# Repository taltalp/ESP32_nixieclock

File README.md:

# ESP32 Nixie Clock

## Overview
Nixie-tube Clock using ESP32 KiCad PCB design and Arduino projects.

## Software Versions
- KiCad 4.0.1 Stable
- Arduino 1.8.2

## Nixie Tube footprints
IN-12 is used in this design and this footprint has 2mm hole * 12 which is designed to use IN-12 pin sockets.

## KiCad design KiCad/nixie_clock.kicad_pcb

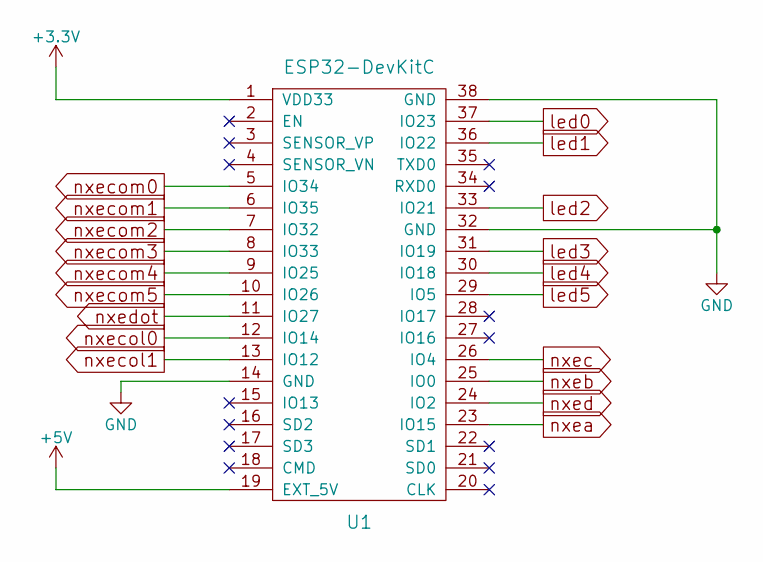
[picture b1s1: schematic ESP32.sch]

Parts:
U1: ESP32-DevKitC; ESP32-DEV-Kit

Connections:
+3V3: U1.1 (VDD33); also elsewhere on the board
+5V: U1.19 (EXT_5V); also elsewhere on the board
GND: U1.14 (GND), U1.32 (GND), U1.38 (GND); also elsewhere on the board
led0: U1.37 (IO23); also elsewhere on the board
led1: U1.36 (IO22); also elsewhere on the board
led2: U1.33 (IO21); also elsewhere on the board
led3: U1.31 (IO19); also elsewhere on the board
led4: U1.30 (IO18); also elsewhere on the board
led5: U1.29 (IO5); also elsewhere on the board
nxea: U1.23 (IO15); also elsewhere on the board
nxeb: U1.25 (IO0); also elsewhere on the board
nxec: U1.26 (IO4); also elsewhere on the board
nxecol0: U1.12 (IO14); also elsewhere on the board
nxecol1: U1.13 (IO12); also elsewhere on the board
nxecom0: U1.5 (IO34); also elsewhere on the board
nxecom1: U1.6 (IO35); also elsewhere on the board
nxecom2: U1.7 (IO32); also elsewhere on the board
nxecom3: U1.8 (IO33); also elsewhere on the board
nxecom4: U1.9 (IO25); also elsewhere on the board
nxecom5: U1.10 (IO26); also elsewhere on the board
nxed: U1.24 (IO2); also elsewhere on the board
nxedot: U1.11 (IO27); also elsewhere on the board

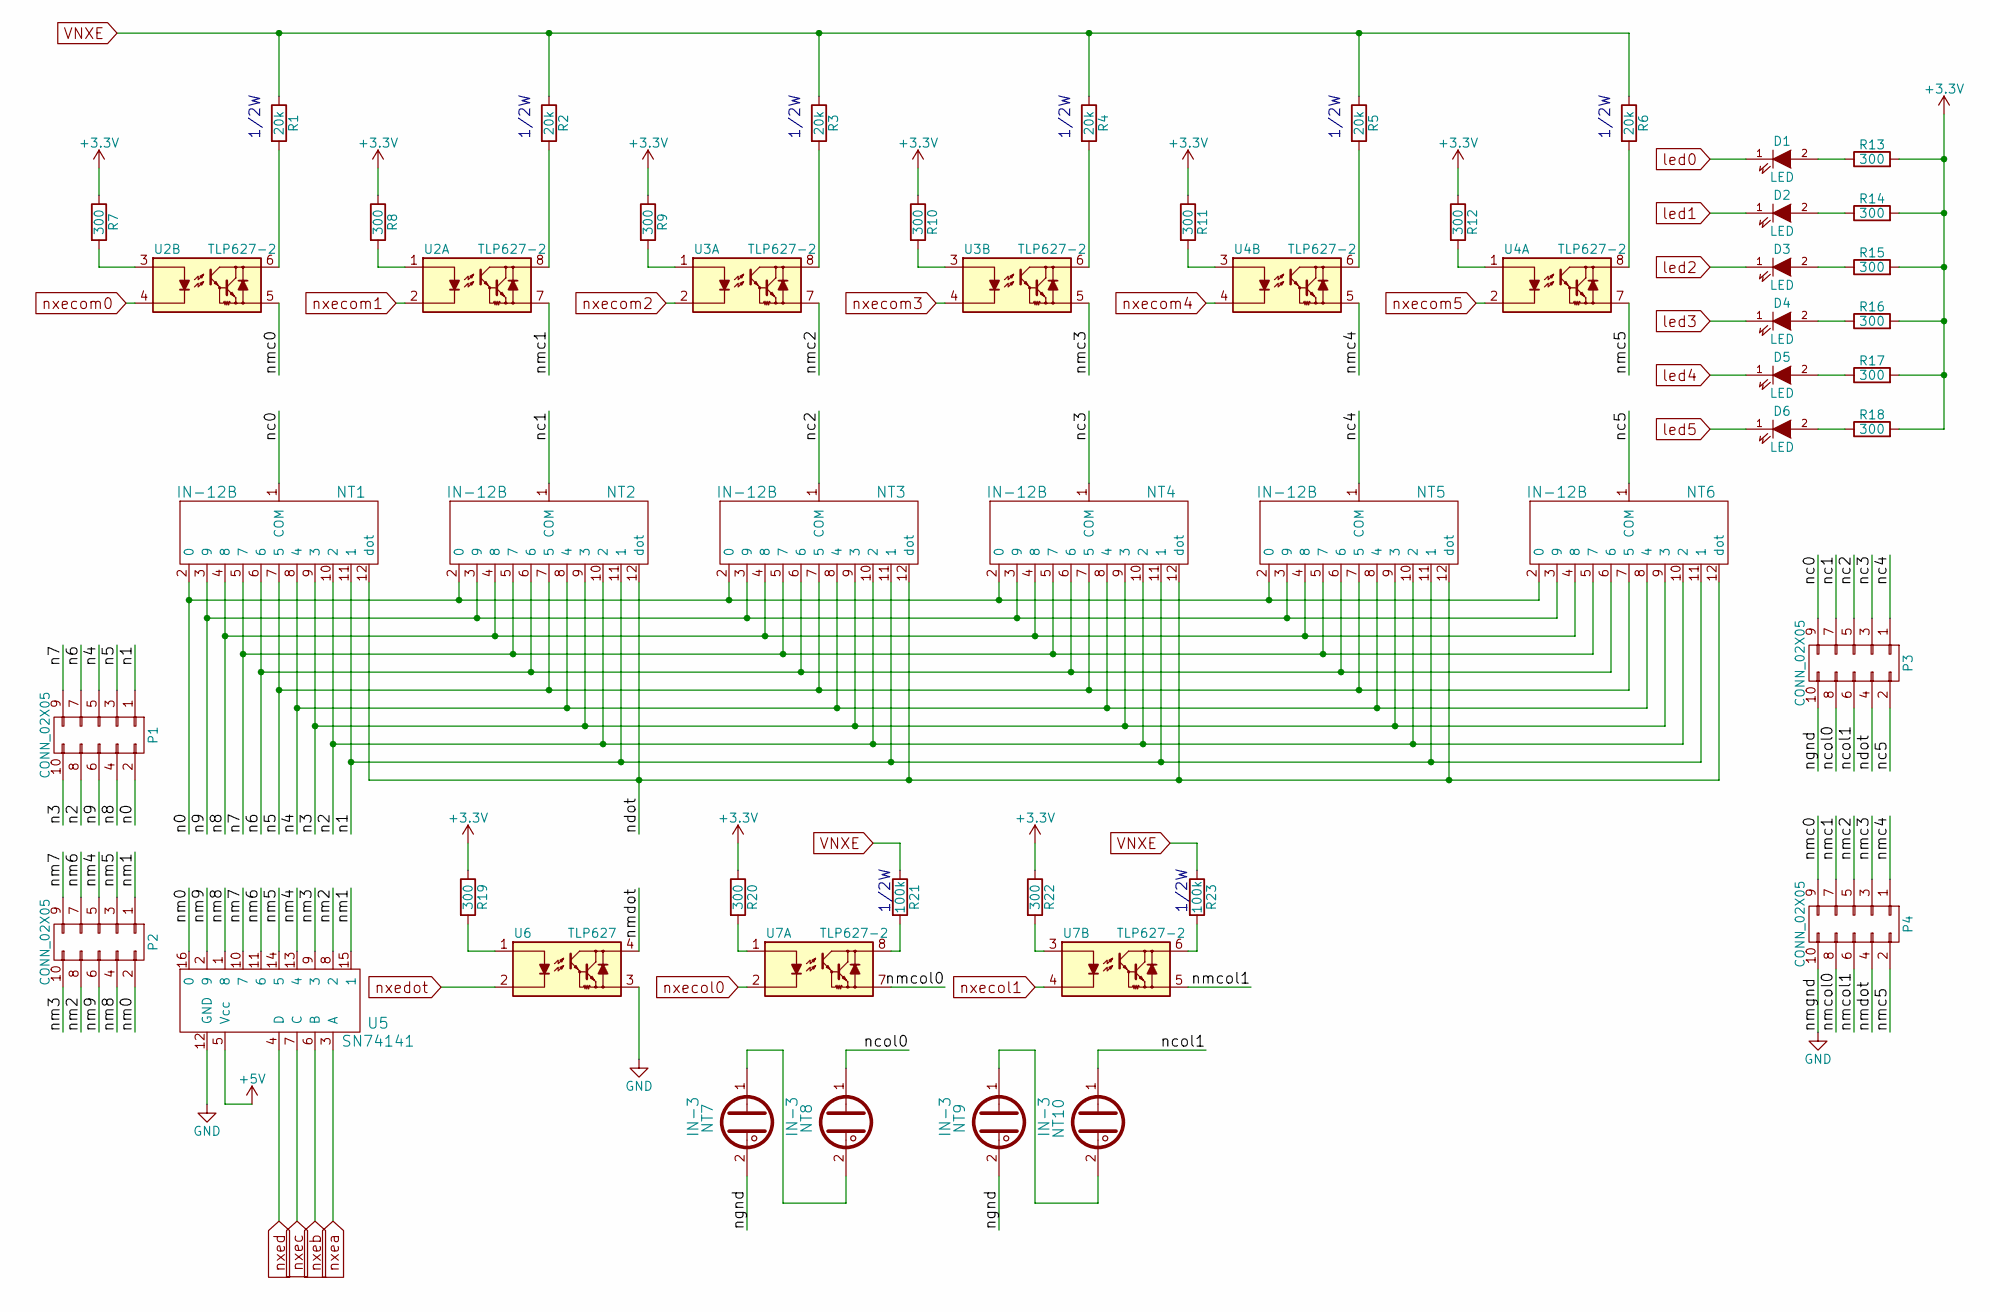
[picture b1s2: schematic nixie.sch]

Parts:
D1, D2, D3, D4, D5, D6: LED; LED_0603
NT1, NT2, NT3, NT4, NT5, NT6: IN-12B; IN-12
NT7, NT8, NT9, NT10: IN-3
P1, P2, P3, P4: CONN_02X05; Socket_Strip_Straight_2x05_Pitch2.54mm
R1, R2, R3, R4, R5, R6: 20k; R_2512
R7, R8, R9, R10, R11, R12, R13, R14, R15, R16, R17, R18, R19, R20, R22: 300; R_0603
R21, R23: 100k; R_2512
U2, U3, U4, U7: TLP627-2; DIP-8_W7.62mm
U5: SN74141; DIP-16_W7.62mm
U6: TLP627; DIP-4_W7.62mm

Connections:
+3V3: R7.1, R8.1, R9.1, R10.1, R11.1, R12.1, R13.2, R14.2, R15.2, R16.2, R17.2, R18.2, R19.1, R20.1, R22.1; also elsewhere on the board
+5V: U5.5 (Vcc); also elsewhere on the board
/nixie/n0: NT1.2 (0), NT2.2 (0), NT3.2 (0), NT4.2 (0), NT5.2 (0), NT6.2 (0), P1.2
/nixie/n1: NT1.11 (1), NT2.11 (1), NT3.11 (1), NT4.11 (1), NT5.11 (1), NT6.11 (1), P1.1
/nixie/n2: NT1.10 (2), NT2.10 (2), NT3.10 (2), NT4.10 (2), NT5.10 (2), NT6.10 (2), P1.8
/nixie/n3: NT1.9 (3), NT2.9 (3), NT3.9 (3), NT4.9 (3), NT5.9 (3), NT6.9 (3), P1.10
/nixie/n4: NT1.8 (4), NT2.8 (4), NT3.8 (4), NT4.8 (4), NT5.8 (4), NT6.8 (4), P1.5
/nixie/n5: NT1.7 (5), NT2.7 (5), NT3.7 (5), NT4.7 (5), NT5.7 (5), NT6.7 (5), P1.3
/nixie/n6: NT1.6, NT2.6, NT3.6, NT4.6, NT5.6, NT6.6, P1.7
/nixie/n7: NT1.5 (7), NT2.5 (7), NT3.5 (7), NT4.5 (7), NT5.5 (7), NT6.5 (7), P1.9
/nixie/n8: NT1.4 (8), NT2.4 (8), NT3.4 (8), NT4.4 (8), NT5.4 (8), NT6.4 (8), P1.4
/nixie/n9: NT1.3 (9), NT2.3 (9), NT3.3 (9), NT4.3 (9), NT5.3 (9), NT6.3 (9), P1.6
/nixie/nc0: NT1.1 (COM), P3.9
/nixie/nc1: NT2.1 (COM), P3.7
/nixie/nc2: NT3.1 (COM), P3.5
/nixie/nc3: NT4.1 (COM), P3.3
/nixie/nc4: NT5.1 (COM), P3.1
/nixie/nc5: NT6.1 (COM), P3.2
/nixie/ncol0: NT8.1, P3.8
/nixie/ncol1: NT10.1, P3.6
/nixie/ndot: NT1.12 (dot), NT2.12 (dot), NT3.12 (dot), NT4.12 (dot), NT5.12 (dot), NT6.12 (dot), P3.4
/nixie/ngnd: NT7.2, NT9.2, P3.10
/nixie/nm0: P2.2, U5.16 (0)
/nixie/nm1: P2.1, U5.15 (1)
/nixie/nm2: P2.8, U5.8 (2)
/nixie/nm3: P2.10, U5.9 (3)
/nixie/nm4: P2.5, U5.13 (4)
/nixie/nm5: P2.3, U5.14 (5)
/nixie/nm6: P2.7, U5.11 (6)
/nixie/nm7: P2.9, U5.10 (7)
/nixie/nm8: P2.4, U5.1 (8)
/nixie/nm9: P2.6, U5.2 (9)
/nixie/nmc0: P4.9, U2.5
/nixie/nmc1: P4.7, U2.7
/nixie/nmc2: P4.5, U3.7
/nixie/nmc3: P4.3, U3.5
/nixie/nmc4: P4.1, U4.5
/nixie/nmc5: P4.2, U4.7
/nixie/nmcol0: P4.8, U7.7
/nixie/nmcol1: P4.6, U7.5
/nixie/nmdot: P4.4, U6.4
GND: P4.10, U5.12 (GND), U6.3; also elsewhere on the board
unnamed: D1.2 (A), R13.1
unnamed: D2.2 (A), R14.1
unnamed: D3.2 (A), R15.1
unnamed: D4.2 (A), R16.1
unnamed: D5.2 (A), R17.1
unnamed: D6.2 (A), R18.1
unnamed: NT7.1, NT8.2
unnamed: NT9.1, NT10.2
unnamed: R1.2, U2.6
unnamed: R2.2, U2.8
unnamed: R3.2, U3.8
unnamed: R4.2, U3.6
unnamed: R5.2, U4.6
unnamed: R6.2, U4.8
unnamed: R7.2, U2.3
unnamed: R8.2, U2.1
unnamed: R9.2, U3.1
unnamed: R10.2, U3.3
unnamed: R11.2, U4.3
unnamed: R12.2, U4.1
unnamed: R19.2, U6.1
unnamed: R20.2, U7.1
unnamed: R21.2, U7.8
unnamed: R22.2, U7.3
unnamed: R23.2, U7.6
VNXE: R1.1, R2.1, R3.1, R4.1, R5.1, R6.1, R21.1, R23.1; also elsewhere on the board
led0: D1.1 (K); also elsewhere on the board
led1: D2.1 (K); also elsewhere on the board
led2: D3.1 (K); also elsewhere on the board
led3: D4.1 (K); also elsewhere on the board
led4: D5.1 (K); also elsewhere on the board
led5: D6.1 (K); also elsewhere on the board
nxea: U5.3 (A); also elsewhere on the board
nxeb: U5.6 (B); also elsewhere on the board
nxec: U5.7 (C); also elsewhere on the board
nxecol0: U7.2; also elsewhere on the board
nxecol1: U7.4; also elsewhere on the board
nxecom0: U2.4; also elsewhere on the board
nxecom1: U2.2; also elsewhere on the board
nxecom2: U3.2; also elsewhere on the board
nxecom3: U3.4; also elsewhere on the board
nxecom4: U4.4; also elsewhere on the board
nxecom5: U4.2; also elsewhere on the board
nxed: U5.4 (D); also elsewhere on the board
nxedot: U6.2; also elsewhere on the board

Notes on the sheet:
1/2W

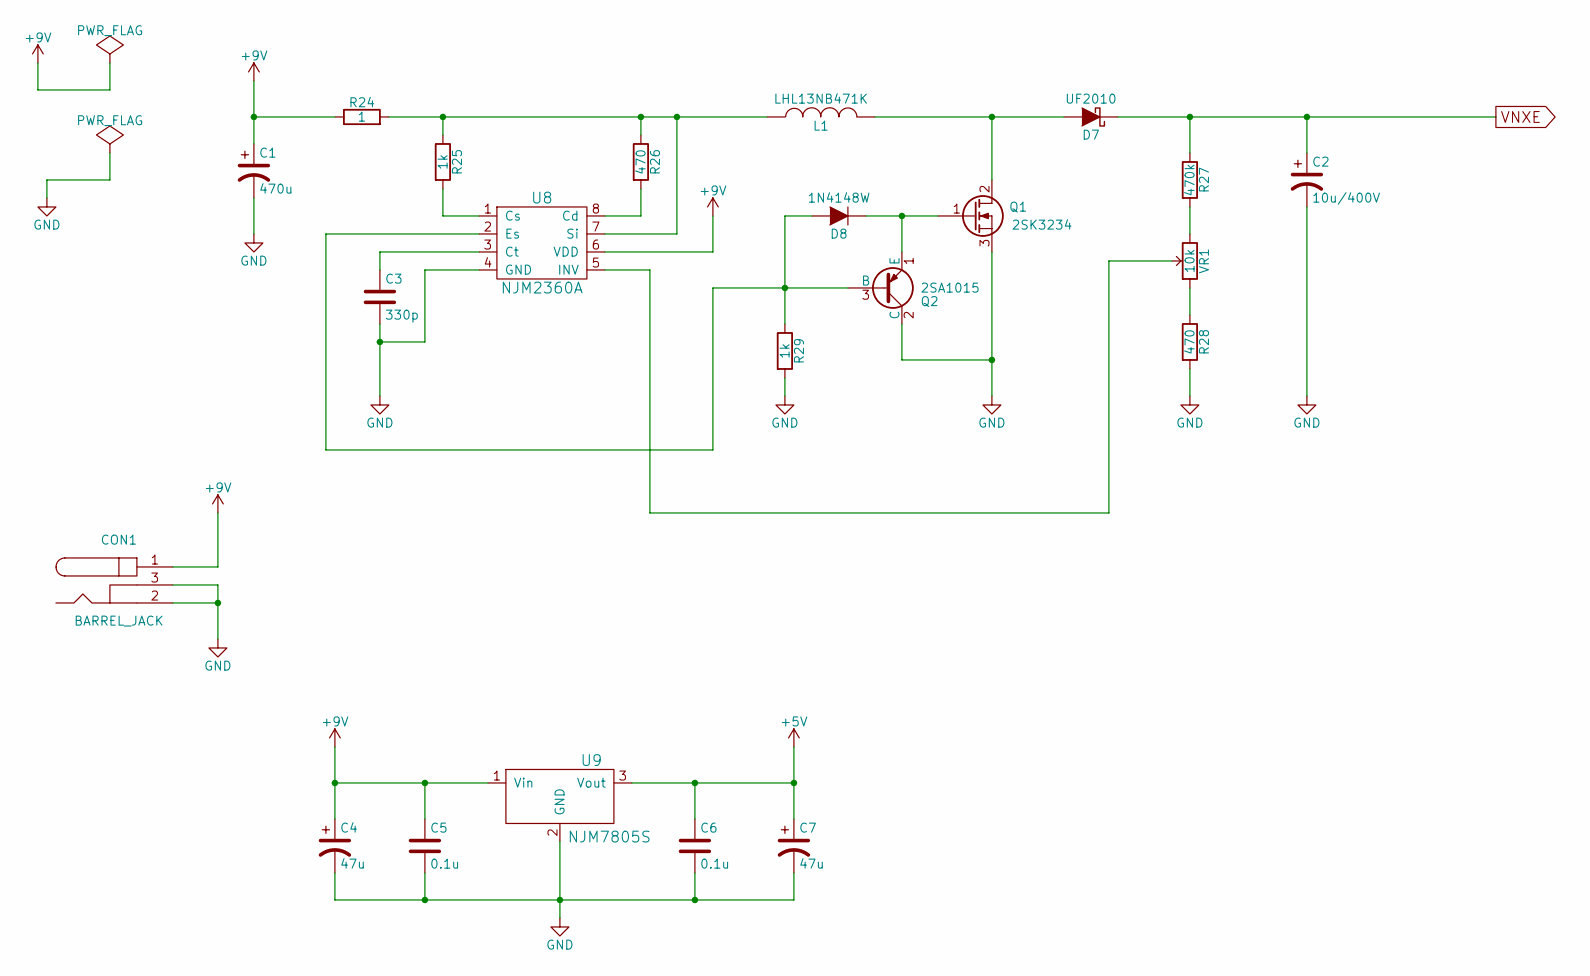
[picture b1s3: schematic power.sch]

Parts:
C1: 470u; CP_Radial_D7.5mm_P2.50mm
C2: 10u/400V; CP_Radial_D10.0mm_P5.00mm
C3: 330p; C_0603
C4, C7: 47u; C_3225
C5, C6: 0.1u; C_0603
CON1: BARREL_JACK
D7: UF2010; D_A-405_P10.16mm_Horizontal
D8: 1N4148W; D_SOD-123
L1: LHL13NB471K
Q1: 2SK3234; TO-220-3_Horizontal
Q2: 2SA1015; TO-92_Inline_Wide
R24: 1; R_2512
R25, R29: 1k; R_1206
R26, R28: 470; R_1206
R27: 470k; R_1206
U8: NJM2360A; DIP-8_W7.62mm
U9: NJM7805S; TO-252-3_TabPin2
VR1: 10k; Potentiometer_Triwood_RM-065

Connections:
+5V: C6.1, C7.1, U9.3 (Vout); also elsewhere on the board
+9V: C1.1, C4.1, C5.1, CON1.1, R24.1, U8.6 (VDD), U9.1 (Vin)
GND: C1.2, C2.2, C3.2, C4.2, C5.2, C6.2, C7.2, CON1.2, CON1.3, Q1.3 (S), Q2.2 (C), R28.2, R29.2, U8.4 (GND), U9.2 (GND); also elsewhere on the board
unnamed: C3.1, U8.3 (Ct)
unnamed: D7.2 (A), L1.2, Q1.2 (D)
unnamed: D8.1 (K), Q1.1 (G), Q2.1 (E)
unnamed: D8.2 (A), Q2.3 (B), R29.1, U8.2 (Es)
unnamed: L1.1, R24.2, R25.1, R26.1, U8.7 (Si)
unnamed: R25.2, U8.1 (Cs)
unnamed: R26.2, U8.8 (Cd)
unnamed: R27.2, VR1.1
unnamed: R28.1, VR1.2
unnamed: U8.5 (INV), VR1.3
VNXE: C2.1, D7.1 (K), R27.1; also elsewhere on the board

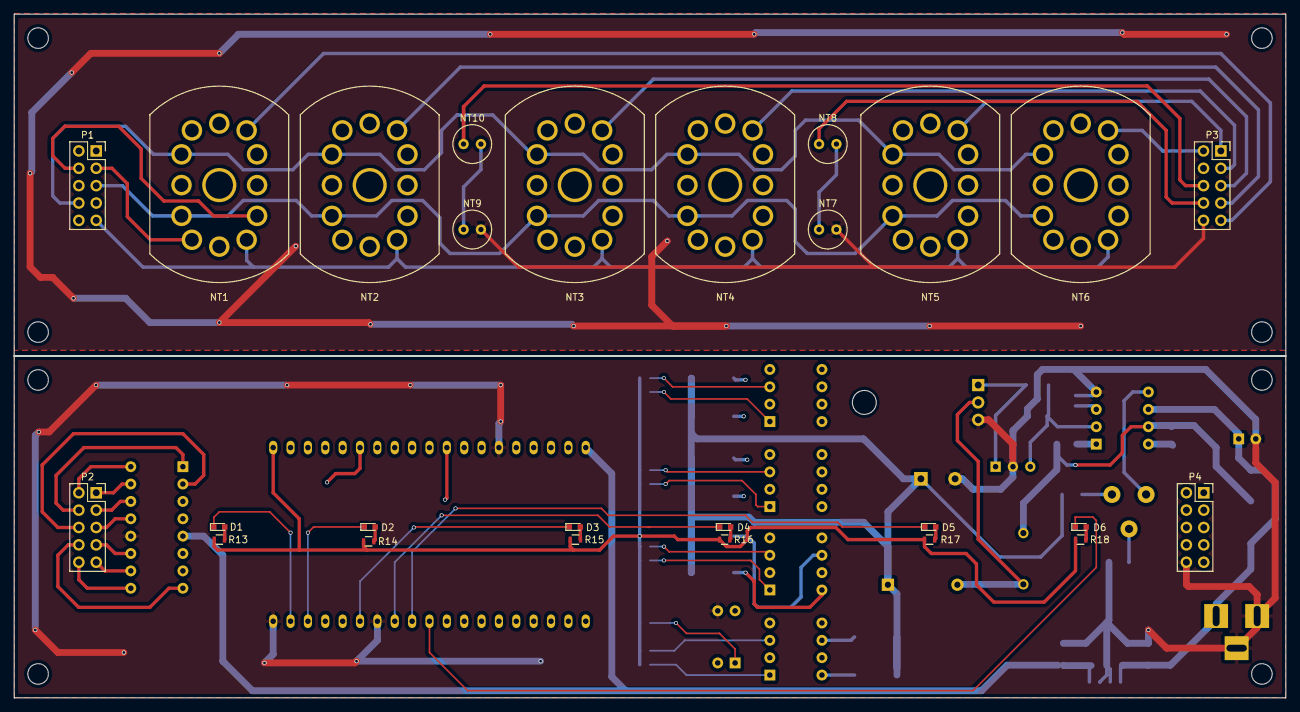
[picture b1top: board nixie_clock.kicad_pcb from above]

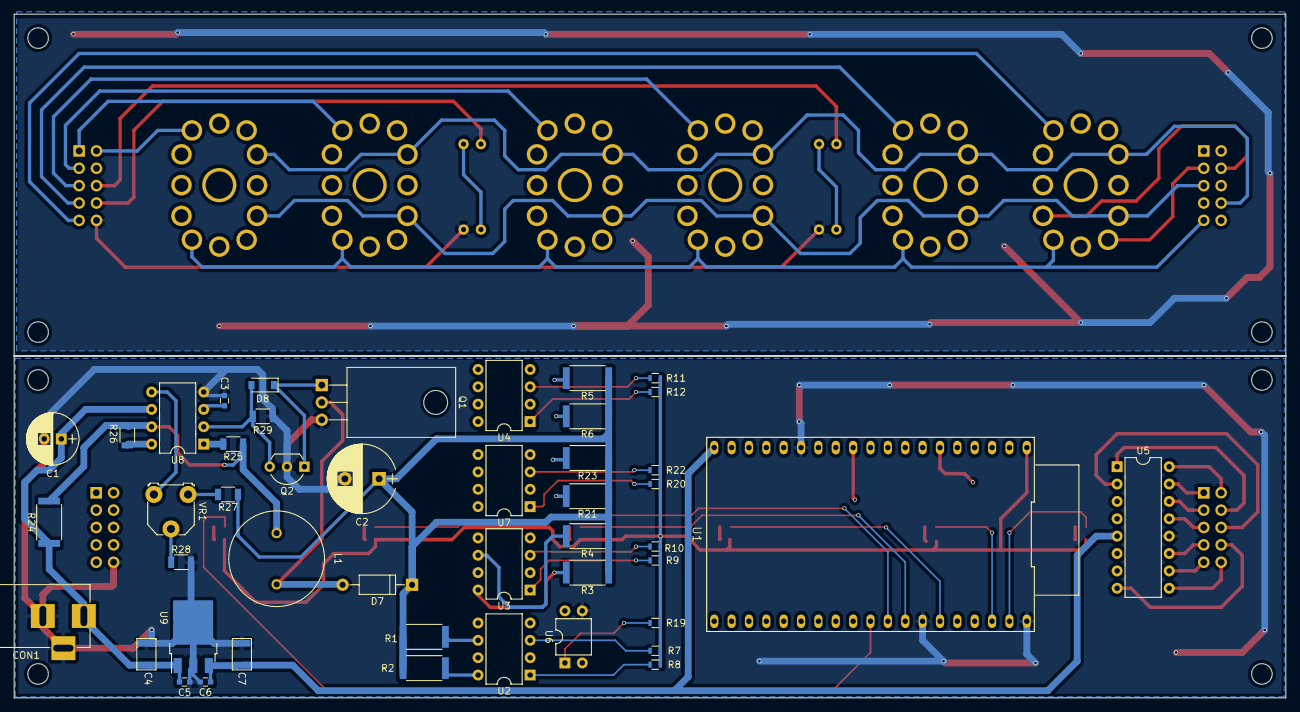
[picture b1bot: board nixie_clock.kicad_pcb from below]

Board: 4 copper layers, 186.0 x 100.0 mm, 72 parts (46 on the bottom side), 98 nets.

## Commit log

2017-10-15 add gitignores
2017-10-15 add KiCad Designs
2017-10-15 modified readme
2017-10-15 modified readme.md
2017-10-15 add esp32 NTP client project
2017-10-16 add power schematic
2017-10-16 add nixie functions
2017-10-19 change schematics
2017-10-20 add pcb design
2017-10-21 change some pcb packages
2017-10-23 change footprints
2017-10-23 many changes
2017-10-23 change readme
2017-10-24 add connectors
2017-10-24 add edge cuts
2017-10-25 place components
2017-10-26 change pcb designs
2017-10-27 finish route
2017-10-27 change pcb
